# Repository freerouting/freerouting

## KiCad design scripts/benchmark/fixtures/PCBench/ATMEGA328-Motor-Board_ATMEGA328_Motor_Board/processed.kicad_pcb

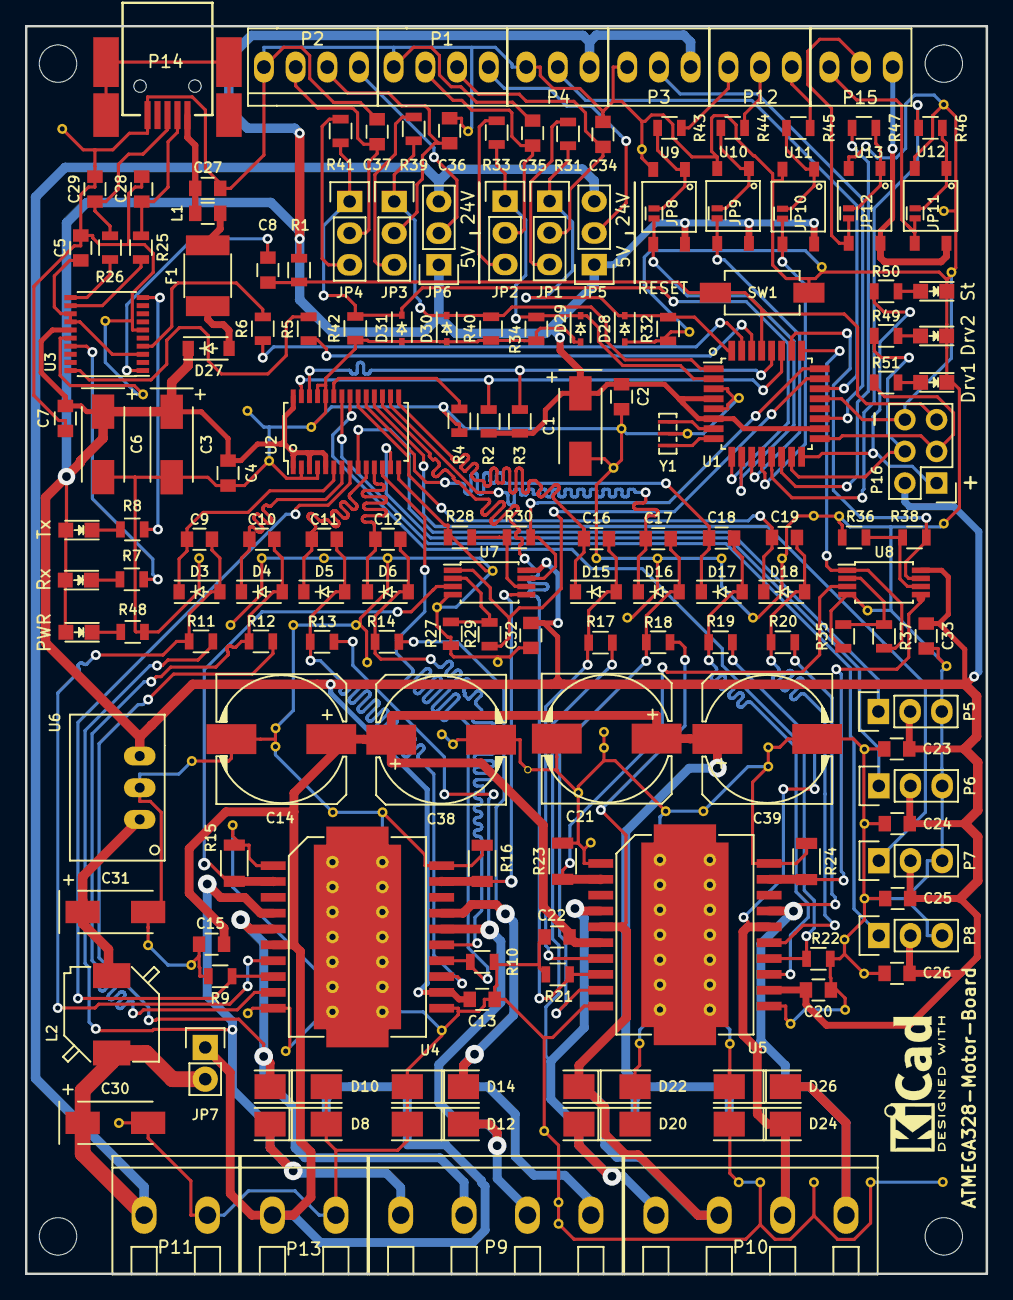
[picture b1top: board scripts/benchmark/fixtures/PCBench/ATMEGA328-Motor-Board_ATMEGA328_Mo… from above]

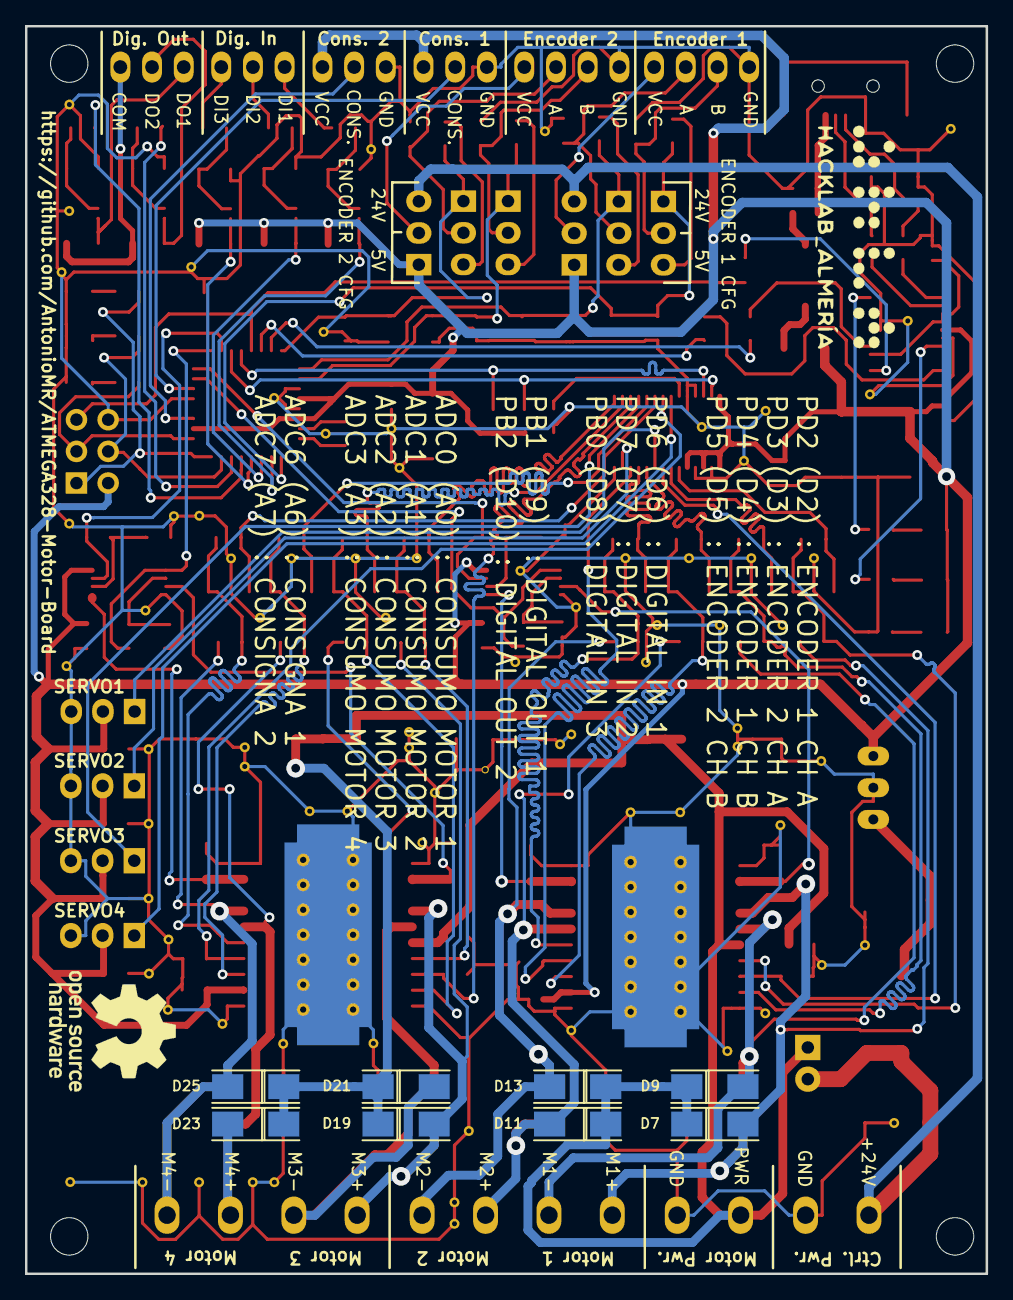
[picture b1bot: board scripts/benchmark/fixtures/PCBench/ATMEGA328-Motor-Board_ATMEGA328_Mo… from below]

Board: 2 copper layers, 77.0 x 100.0 mm, 254 parts (8 on the bottom side), 111 nets.

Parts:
C1, C3, C6, C30, C31: 4,7u; TantalC_SizeC_EIA-6032_Wave
C2, C4, C5, C7, C8, C13, C15, C20, C22, C23, C24, C25, C26, C32, C33, C34, C35, C36, C37: 100n; C_0805
C9, C10, C11, C12, C16, C17, C18, C19: 1,5n; C_0805
C14, C21, C38, C39: 220u; c_elec_10x10
C27: 10n; C_0805
C28, C29: 0,047n; C_0805
D1, D2, D33, D34, D35: Rojo; LED_0805
D3, D4, D5, D6, D15, D16, D17, D18: 1N4148; SOD-123
D7, D8, D9, D10, D11, D12, D13, D14, D19, D20, D21, D22, D23, D24, D25, D26: 10MQ100; DO-214AC
D27: MBR0520; SOD-123
D28, D29, D30, D31: PDZ5; SOD-323
D32: LED; LED_0805
F1: 500 mA; R_1812
Gnd-Via: VAL**; Gnd-Via
Gnd-Via_2, Gnd-Via_3, Gnd-Via_4, Gnd-Via_5, Gnd-Via_6, Gnd-Via_7, Gnd-Via_8, Gnd-Via_9, Gnd-Via_10, Gnd-Via_11, Gnd-Via_12, Gnd-Via_13, Gnd-Via_14, Gnd-Via_15, Gnd-Via_16, Gnd-Via_17, Gnd-Via_18, Gnd-Via_19, Gnd-Via_20, Gnd-Via_21, Gnd-Via_22, Gnd-Via_23, Gnd-Via_24, Gnd-Via_25, Gnd-Via_26, Gnd-Via_27, Gnd-Via_28, Gnd-Via_29, Gnd-Via_30, Gnd-Via_31, Gnd-Via_32, Gnd-Via_34, Gnd-Via_35, Gnd-Via_36, Gnd-Via_37, Gnd-Via_38, Gnd-Via_39, Gnd-Via_40, Gnd-Via_41, Gnd-Via_42, Gnd-Via_43, Gnd-Via_44, Gnd-Via_45, Gnd-Via_46, Gnd-Via_47, Gnd-Via_48, Gnd-Via_49, Gnd-Via_50, Gnd-Via_51, Gnd-Via_52, Gnd-Via_53, Gnd-Via_54, Gnd-Via_55, Gnd-Via_56, Gnd-Via_57, Gnd-Via_58, Gnd-Via_59, Gnd-Via_60, Gnd-Via_61, Gnd-Via_62, Gnd-Via_63, Gnd-Via_64, Gnd-Via_65, Gnd-Via_66, Gnd-Via_67, Gnd-Via_68, Gnd-Via_69, Gnd-Via_70, Gnd-Via_71, Gnd-Via_72, Gnd-Via_73, Gnd-Via_74, Gnd-Via_75, Gnd-Via_76, Gnd-Via_77, Gnd-Via_78, Gnd-Via_79, Gnd-Via_80, Gnd-Via_81, Gnd-Via_82, Gnd-Via_83, Gnd-Via_84: VAL**; Gnd-Via
JP1, JP2, JP3, JP4, JP5, JP6: JUMPER_3; Pin_Header_Straight_1x03
JP7: JUMPER_2; Pin_Header_Straight_1x02
JP8, JP9, JP10, JP11, JP12: Jumper_NO_Small; JMP_0603
L1: BLM21; C_0805
L2: 10u; FERROCORE_SMD_0703
P1, P2: CONN_01X04; PhoenixContact_MPT_0,5_4-2,54
P3, P4, P12, P15: CONN_01X03; PhoenixContact_MPT_0,5_3-2,54
P5, P6, P7, P8: CONN_01X03; Pin_Header_Straight_1x03
P9, P10: CONN_01X04; PhoenixContact_mkdsn_4_5.08
P11, P13: CONN_01X02; PhoenixContact_mkdsn_2_5.08
P14: USB_MINI; usb_mini_molex_675031020
P16: CONN_02X03; Pin_Header_Straight_2x03
R1, R2, R3, R5, R6: 1K; R_0805
R4, R9, R10, R11, R12, R13, R14, R17, R18, R19, R20, R21, R22, R27, R28, R32, R34, R35, R36, R40, R42: 10K; R_0805
R7, R8, R49, R50, R51: 270; R_0805
R15, R16, R23, R24: 0.02; R_1206
R25, R26: 22R; R_0805
R29, R30, R37, R38: 23K2; R_0805
R31, R33, R39, R41: 38K3; R_0805
R43, R44, R45, R46, R47, R48: R; R_0805
SW1: Pulsador_2p; CANAL_ELECTRONIC_DTSM-31N-B
U1: ATMEGA328; TQFP-32_7x7mm_Pitch0.8mm
U2: PCA9685; TSSOP-28_4.4x9.7mm_Pitch0.65mm
U3: FT231X; SSOP-20_4.4x6.5mm_Pitch0.65mm
U4, U5: L298P; L298_PowerSO20
U6: TSR_1; TSR-1
U7, U8: LM2903; TSSOP-8_4.4x3mm_Pitch0.65mm
U9, U10, U11: VOM617A; SOP-4
U12, U13: ASSR-1218; SOP-4
Y1: 16MHz; Murata_CSTCE_V_A

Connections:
+5V: C1.1, C2.1, C3.1, C4.1, C6.1, C7.1, C13.2, C20.2, C23.1, C24.1, C25.1, C26.1, C32.1, C33.1, D1.2, D2.2, D27.1, D32.2, JP5.1, JP6.1, P3.1, P4.1, P5.2, P6.2, P7.2, P8.2, P16.2, R1.1, R2.1, R3.1, U1.4, U1.6, U1.18, U2.1, U2.3, U2.5, U2.28, U3.15, U4.12, U5.12, U6.3, U7.8, U8.8, U9.4, U10.4, U11.4
+24V: C30.1, JP5.3, JP6.3, JP7.2, L2.1, P11.1
/Control/Rx: R5.1, U3.20
/Control/SCL: R3.2, U1.28, U2.26
/Control/SDA: R2.2, U1.27, U2.27
/Control/Tx: R6.1, U3.4
/Pines/XUSB: C27.1, L1.2, P14.1
/Potencia/Motor1_A_in: C9.1, D3.2, R11.2, U4.7
/Potencia/Motor1_B_in: C10.1, D4.2, R12.2, U4.9
/Potencia/Motor2_A_in: C11.1, D5.2, R13.2, U4.13
/Potencia/Motor2_B_in: C12.1, D6.2, R14.2, U4.15
/Potencia/Motor3_A_in: C16.1, D15.2, R17.2, U5.7
/Potencia/Motor3_B_in: C17.1, D16.2, R18.2, U5.9
/Potencia/Motor4_A_in: C18.1, D17.2, R19.2, U5.13
/Potencia/Motor4_B_in: C19.1, D18.2, R20.2, U5.15
CONSIGNA1: P3.2, U1.19
CONSIGNA2: P4.2, U1.22
D+: R26.1, U3.11
D-: R25.1, U3.12
DI1: P12.3, R43.2
DI2: P12.2, R44.2
DI3: P12.1, R45.2
DO1: JP11.2, P15.3, U12.3
DO2: JP12.2, P15.2, U13.3
DO_COM: P15.1, U12.4, U13.4
ENC1_A: C34.1, JP1.2, P1.2
ENC1_A2: D28.1, JP1.1, R31.1, R32.1, U1.32
ENC1_B: C35.1, JP2.2, P1.3
ENC1_B2: D29.1, JP2.1, R33.1, R34.1, U1.2
ENC1_PWR: JP5.2, P1.1
ENC2_A: C36.1, JP3.2, P2.2
ENC2_A2: D30.1, JP3.1, R39.1, R40.1, U1.1
ENC2_B: C37.1, JP4.2, P2.3
ENC2_B2: D31.1, JP4.1, R41.1, R42.1, U1.9
ENC2_PWR: JP6.2, P2.1
GND: C1.2, C2.2, C3.2, C4.2, C5.2, C6.2, C7.2, C13.1, C14.2, C15.2, C20.1, C21.2, C22.2, C23.2, C24.2, C25.2, C26.2, C27.2, C28.2, C29.2, C30.2, C31.2, C32.2, C33.2, C34.2, C35.2, C36.2, C37.2, C38.2, C39.2, D8.2, D10.2, D12.2, D14.2, D20.2, D22.2, D24.2, D26.2, D28.2, D29.2, D30.2, D31.2, D33.1, D34.1, D35.1, Gnd-Via.1, Gnd-Via_2.1, Gnd-Via_3.1, Gnd-Via_4.1, Gnd-Via_5.1, Gnd-Via_10.1, Gnd-Via_11.1, Gnd-Via_12.1, Gnd-Via_13.1, Gnd-Via_14.1, Gnd-Via_15.1, Gnd-Via_16.1, Gnd-Via_17.1, Gnd-Via_18.1, Gnd-Via_19.1, Gnd-Via_20.1, Gnd-Via_21.1, Gnd-Via_22.1, Gnd-Via_23.1, Gnd-Via_24.1, Gnd-Via_25.1, Gnd-Via_26.1, Gnd-Via_27.1, Gnd-Via_28.1, Gnd-Via_29.1, Gnd-Via_30.1, Gnd-Via_31.1, Gnd-Via_32.1, Gnd-Via_34.1, Gnd-Via_35.1, Gnd-Via_36.1, Gnd-Via_37.1, Gnd-Via_38.1, Gnd-Via_39.1, Gnd-Via_40.1, Gnd-Via_41.1, Gnd-Via_42.1, Gnd-Via_43.1, Gnd-Via_44.1, Gnd-Via_45.1, Gnd-Via_46.1, Gnd-Via_47.1, Gnd-Via_48.1, Gnd-Via_49.1, Gnd-Via_50.1, Gnd-Via_51.1, Gnd-Via_52.1, Gnd-Via_53.1, Gnd-Via_54.1, Gnd-Via_55.1, Gnd-Via_56.1, Gnd-Via_57.1, Gnd-Via_58.1, Gnd-Via_59.1, Gnd-Via_60.1, Gnd-Via_61.1, Gnd-Via_62.1, Gnd-Via_63.1, Gnd-Via_64.1, Gnd-Via_65.1, Gnd-Via_66.1, Gnd-Via_67.1, Gnd-Via_68.1, Gnd-Via_69.1, Gnd-Via_70.1, Gnd-Via_71.1, Gnd-Via_72.1, Gnd-Via_73.1, Gnd-Via_74.1, Gnd-Via_75.1, Gnd-Via_76.1, Gnd-Via_77.1, Gnd-Via_78.1, Gnd-Via_79.1, Gnd-Via_80.1, Gnd-Via_81.1, Gnd-Via_82.1, Gnd-Via_83.1, Gnd-Via_84.1, P1.4, P2.4, P3.3, P4.3, P5.3, P6.3, P7.3, P8.3, P11.2, P13.2, P14.5, P16.6, R4.2, R9.2, R10.2, R15.2, R16.2, R21.2, R22.2, R23.2, R24.2, R27.2, R28.2, R32.2, R34.2, R35.2, R36.2, R40.2, R42.2, R48.2, SW1.1, U1.3, U1.5, U1.21, U2.2, U2.4, U2.14, U2.24, U2.25, U3.6, U3.16, U4.1, U4.10, U4.11, U4.20, U5.1, U5.10, U5.11, U5.20, U6.2, U7.4, U8.4, U9.2, U10.2, U11.2, U12.2, U13.2, Y1.2
MISO: P16.1, R50.1, U1.16
MOSI: P16.4, R49.1, U1.15
MOTOR1_A: C9.2, D3.1, U2.6
MOTOR1_B: C10.2, D4.1, U2.7
MOTOR1_CURRENT: R29.1, U1.23, U7.1
MOTOR1_EN: R9.1, U2.8, U4.8
MOTOR1_SENSE: R15.1, U4.2, U7.3
MOTOR2_A: C11.2, D5.1, U2.10
MOTOR2_B: C12.2, D6.1, U2.11
MOTOR2_CURRENT: R30.1, U1.24, U7.7
MOTOR2_EN: R10.1, U2.12, U4.14
MOTOR2_SENSE: R16.1, U4.19, U7.5
MOTOR3_A: C16.2, D15.1, U2.15
MOTOR3_B: C17.2, D16.1, U2.16
MOTOR3_CURRENT: R37.1, U1.25, U8.1
MOTOR3_EN: R21.1, U2.17, U5.8
MOTOR3_SENSE: R23.1, U5.2, U8.3
MOTOR4_A: C18.2, D17.1, U2.19
MOTOR4_B: C19.2, D18.1, U2.20
MOTOR4_CURRENT: R38.1, U1.26, U8.7
MOTOR4_EN: R22.1, U2.21, U5.14
MOTOR4_SENSE: R24.1, U5.19, U8.5
Motor1+: D7.2, D8.1, P9.1, R11.1, U4.4
Motor1-: D9.2, D10.1, P9.2, R12.1, U4.5
Motor2+: D11.2, D12.1, P9.3, R13.1, U4.16
Motor2-: D13.2, D14.1, P9.4, R14.1, U4.17
Motor3+: D19.2, D20.1, P10.1, R17.1, U5.4
Motor3-: D21.2, D22.1, P10.2, R18.1, U5.5
Motor4+: D23.2, D24.1, P10.3, R19.1, U5.16
Motor4-: D25.2, D26.1, P10.4, R20.1, U5.17
unnamed: C5.1, U3.3, U3.13, U3.14
unnamed: C8.2, U3.1
unnamed: C28.1, P14.2, R25.2
unnamed: C29.1, P14.3, R26.2
unnamed: C31.1, L2.2, U6.1
unnamed: D1.1, R7.1
unnamed: D2.1, R8.2
unnamed: D32.1, R48.1
unnamed: D33.2, R49.2
unnamed: D34.2, R50.2
unnamed: D35.2, R51.2
unnamed: F1.1, L1.1
unnamed: JP1.3, R31.2
unnamed: JP2.3, R33.2
unnamed: JP3.3, R39.2
unnamed: JP4.3, R41.2
unnamed: JP8.1, R43.1, U9.1
unnamed: JP9.1, R44.1, U10.1
unnamed: JP10.1, R45.1, U11.1
unnamed: JP11.1, R46.1, U12.1
unnamed: JP12.1, R47.1, U13.1
unnamed: R4.1, U2.23
unnamed: R5.2, U1.30
unnamed: R6.2, U1.31
unnamed: R7.2, U3.17
unnamed: R8.1, U3.10
unnamed: R27.1, R29.2, U7.2
unnamed: R28.1, R30.2, U7.6
unnamed: R35.1, R37.2, U8.2
unnamed: R36.1, R38.2, U8.6
unnamed: U1.7, Y1.1
unnamed: U1.8, Y1.3
RESET: C8.1, P16.5, R1.2, SW1.2, U1.29
SCK: P16.3, R51.1, U1.17
SERVO1: P5.1, U2.9
SERVO2: P6.1, U2.13
SERVO3: P7.1, U2.18
SERVO4: P8.1, U2.22
VSS: C14.1, C15.1, C21.1, C22.1, C38.1, C39.1, D7.1, D9.1, D11.1, D13.1, D19.1, D21.1, D23.1, D25.1, JP7.1, P13.1, U4.6, U5.6
VUSB: D27.2, F1.2
uC_DI1: JP8.2, U1.10, U9.3
uC_DI2: JP9.2, U1.11, U10.3
uC_DI3: JP10.2, U1.12, U11.3
uC_DO1: R46.2, U1.13
uC_DO2: R47.2, U1.14

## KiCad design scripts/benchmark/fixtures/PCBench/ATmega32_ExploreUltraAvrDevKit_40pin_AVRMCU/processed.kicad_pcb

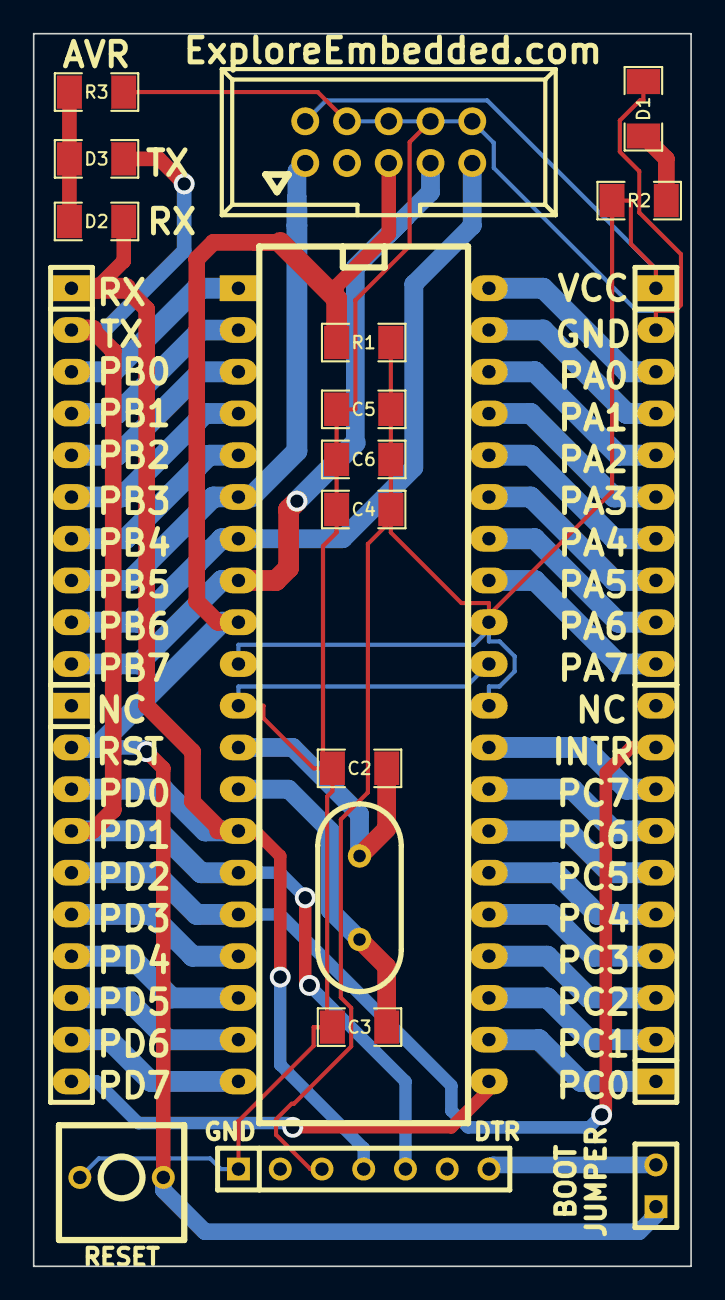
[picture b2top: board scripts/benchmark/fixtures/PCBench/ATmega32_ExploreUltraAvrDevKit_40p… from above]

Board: 2 copper layers, 40.0 x 75.0 mm, 21 parts (0 on the bottom side), 40 nets.

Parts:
C2, C3: 22pF; SM1206
C4, C5, C6: 0.1uF; SM1206
D1, D2, D3: LED; SM1206
IC1: ATMEGA32-P; DIP-40__600_ELL
JP1: JUMPER; SIL-2
P1: CONN_5X2; VASCH5x2
P2, P3, P4, P5: CONN_10; SIL-10
P6: CONN_7; SIL-7
R1: 10K; SM1206
R2, R3: R; SM1206
SW1: rst; SW_PUSH_SMALL_2pin_xl
X1: 16Mhz; HC-49V

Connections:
/+5V: C4.1, C5.1, C6.1, IC1.10, IC1.30, IC1.32, P1.2, P3.1, P6.3, R1.2, R2.1
/INTR: IC1.16, P2.5, P4.9
/MISO: IC1.7, P1.9, P5.9
/MOSI: IC1.6, P1.1, P5.8
/RX: D2.1, IC1.14, P2.3, P5.1, P6.4
/SCK: IC1.8, P1.7, P5.10
/TX: D3.1, IC1.15, P2.4, P5.2, P6.5
/rst: IC1.9, JP1.1, P1.5, P2.2, R1.1, SW1.1
GND: C2.1, C3.1, C4.2, C5.2, C6.2, D1.2, IC1.11, IC1.31, P1.4, P1.6, P1.8, P1.10, P3.2, P6.1, R3.2, SW1.2
unnamed: IC1.34, P3.9
unnamed: IC1.33, P3.10
unnamed: IC1.35, P3.8
unnamed: IC1.36, P3.7
unnamed: IC1.37, P3.6
unnamed: IC1.39, P3.4
unnamed: IC1.40, P3.3
unnamed: IC1.38, P3.5
unnamed: IC1.20, P2.9
unnamed: IC1.2, P5.4
unnamed: IC1.1, P5.3
unnamed: IC1.21, P2.10
unnamed: IC1.3, P5.5
unnamed: IC1.19, P2.8
unnamed: IC1.18, P2.7
unnamed: IC1.5, P5.7
unnamed: IC1.4, P5.6
unnamed: D2.2, D3.2, R3.1
unnamed: JP1.2, P6.7
unnamed: IC1.17, P2.6
unnamed: D1.1, R2.2
unnamed: C2.2, IC1.12, X1.2
unnamed: IC1.24, P4.3
unnamed: IC1.23, P4.2
unnamed: IC1.22, P4.1
unnamed: IC1.29, P4.8
unnamed: IC1.28, P4.7
unnamed: IC1.27, P4.6
unnamed: IC1.26, P4.5
unnamed: IC1.25, P4.4
unnamed: C3.2, IC1.13, X1.1

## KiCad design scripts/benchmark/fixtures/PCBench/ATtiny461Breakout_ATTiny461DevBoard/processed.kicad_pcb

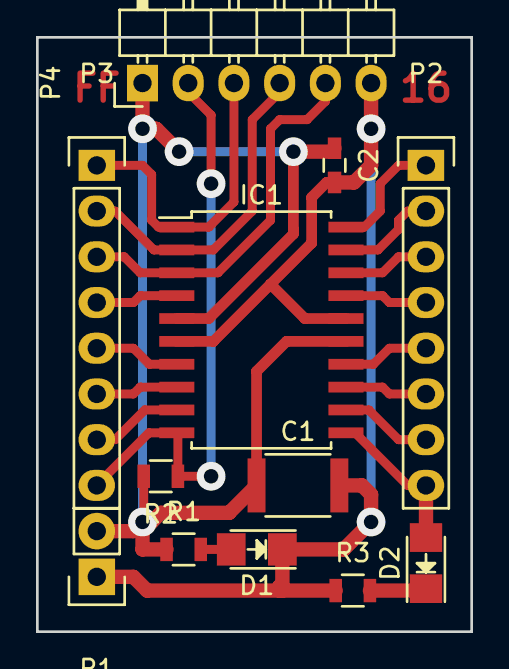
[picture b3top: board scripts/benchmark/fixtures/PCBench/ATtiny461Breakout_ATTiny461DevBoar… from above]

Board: 2 copper layers, 24.1 x 33.0 mm, 12 parts (0 on the bottom side), 20 nets.

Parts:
C1: 10uF; C_1812
C2: 100nF; C_0603_HandSoldering
D1, D2: LED; LED_1206
IC1: ATTINY461-P; SOIC-20_7.5x12.8mm_Pitch1.27mm
P1: CONN_01X02; Pin_Header_Straight_1x02
P2, P3: CONN_01X08; Pin_Header_Straight_1x08
P4: CONN_01X06; Pin_Header_Angled_1x06
R1, R3: 1k; R_0805
R2: R; R_0805

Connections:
GND: C1.2, C2.2, D1.1, IC1.6, IC1.16, P1.1, P4.6, R3.1
unnamed: D1.2, R1.2
unnamed: D2.1, R3.2
unnamed: D2.2, IC1.11, P2.8
unnamed: IC1.1, P3.1, P4.3
unnamed: IC1.2, P3.2, P4.4
unnamed: IC1.3, P3.3, P4.5
unnamed: IC1.4, P3.4
unnamed: IC1.7, P3.5
unnamed: IC1.8, P3.6
unnamed: IC1.9, P3.7
unnamed: IC1.10, P3.8, P4.2, R2.1
unnamed: IC1.12, P2.7
unnamed: IC1.13, P2.6
unnamed: IC1.14, P2.5
unnamed: IC1.17, P2.4
unnamed: IC1.18, P2.3
unnamed: IC1.19, P2.2
unnamed: IC1.20, P2.1
VCC: C1.1, C2.1, IC1.5, IC1.15, P1.2, P4.1, R1.1, R2.2
